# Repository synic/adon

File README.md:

adon
====

AVR Simon Clone

This is a simon clone written for AVR, specifically the ATTiny84a.  The schematic board in eagle/ has been designed to run off of 2 AA batteries, and the chip fuses in fuses.txt set the attiny84a to have a clock of 4mhz, and to have a brown out of 1.8 volts, meaning the batteries should last quite a while before they need to be replaced.

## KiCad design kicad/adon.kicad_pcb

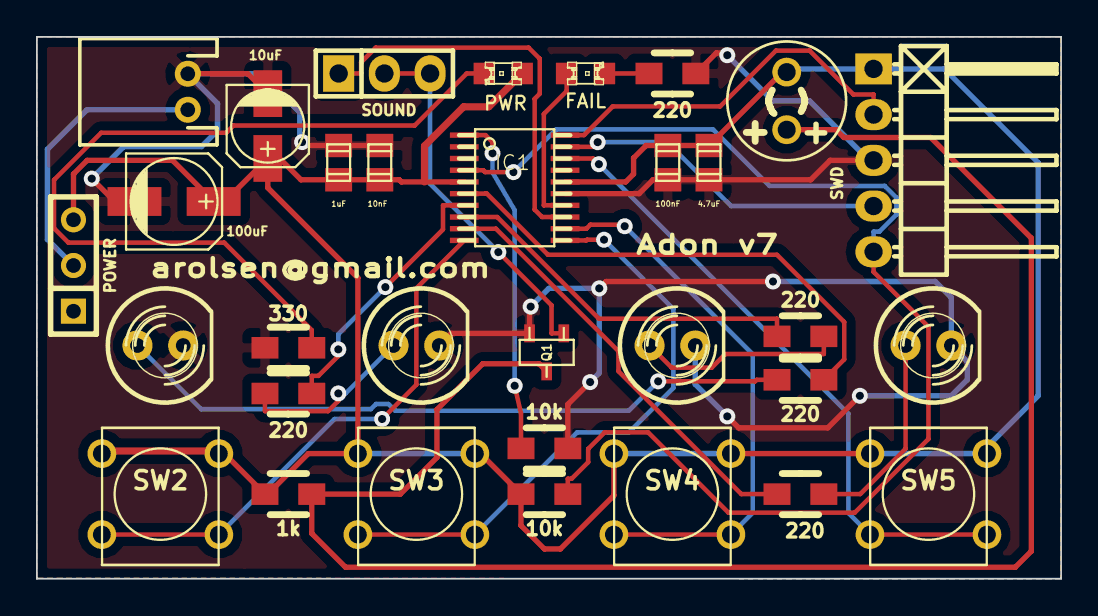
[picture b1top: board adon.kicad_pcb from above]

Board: 2 copper layers, 56.9 x 30.1 mm, 32 parts (0 on the bottom side), 25 nets.

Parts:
C1: 100uF; c_elec_5x5.3
C2: 1uF; c_0805
C3: 4.7uF; c_0805
C4: 10nF; c_0805
C5: 100nF; c_0805
C6: 10uF; c_elec_4x4.5
D1: PWR; LED-0805
D2: LED3; LED-5MM
D3: LED2; LED-5MM
D4: LED1; LED-5MM
D5: LED0; LED-5MM
D6: FAIL; LED-0805
IC1: STM32F030F4; AB2_TSSOP20
JP1: SOUND; Pin_Header_Straight_1x03
P1: BATTERY; jst-2-pth-ra
P3: SWD; Pin_Header_Angled_1x05
Q1: NPN2; sot23transistor
R1, R2: 10k; Resistor_SMD0805_HandSoldering
R3: 330; Resistor_SMD0805_HandSoldering
R4, R5, R6, R7, R9: 220; Resistor_SMD0805_HandSoldering
R8: 1k; Resistor_SMD0805_HandSoldering
SP1: SPEAKER; Buzzer_CUI_INC_CC-1601
SW1: POWER; MICROSWITCH_SPST
SW2: BUTTON0; SW_PUSH_SMALL
SW3: BUTTON1; SW_PUSH_SMALL
SW4: BUTTON2; SW_PUSH_SMALL
SW5: BUTTON3; SW_PUSH_SMALL

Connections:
GND: C1.2, C2.2, C3.1, C4.1, C5.1, C6.2, D2.2, D3.2, D4.2, D5.2, IC1.15, P1.2, P3.3, Q1.2, R1.2, R3.2, R9.2
NRST: IC1.4, P3.5, R2.1
unnamed: D1.2, R3.1
unnamed: D2.1, R4.2
unnamed: D3.1, R5.2
unnamed: D4.1, R6.2
unnamed: D5.1, R7.2
unnamed: D6.1, IC1.14
unnamed: D6.2, R9.1
unnamed: IC1.1, R1.1
unnamed: IC1.6, R7.1
unnamed: IC1.7, R6.1
unnamed: IC1.8, R5.1
unnamed: IC1.9, R4.1
unnamed: IC1.10, SW2.2
unnamed: IC1.11, SW3.2
unnamed: IC1.12, SW4.2
unnamed: IC1.13, JP1.1
unnamed: IC1.18, SW5.2
unnamed: JP1.2, JP1.3, Q1.1
unnamed: P1.1, SW1.2
unnamed: Q1.3, R8.2, SP1.2
SWCLK: IC1.20, P3.2
SWDIO: IC1.19, P3.4
VDD: C1.1, C2.1, C3.2, C4.2, C5.2, C6.1, D1.1, IC1.5, IC1.16, P3.1, R2.2, R8.1, SP1.1, SW1.3, SW2.1, SW3.1, SW4.1, SW5.1

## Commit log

2014-01-17 repo initial
2014-01-17 updated gitignore
2014-01-17 add eagle files
2014-01-17 comments
2014-01-19 woot
2014-01-20 add a 2 second delay after the game turns on to start playing
2014-01-20 add fuse support to Makefile
2014-01-23 done
2014-01-23 hopefully changes for 1mhz
2014-01-23 change bod to 2.7
2014-01-23 woot, got it down to 1mhz by setting prescaler to 64 instead of 1024
2014-01-23 these fuses are for attiny84a, not attiny84
2014-01-23 add the arduino version
2014-01-24 new board files
2014-01-24 add 3aa schematic and board
2014-01-26 board design is done
2014-01-27 add kicad files
2014-02-02 switch to avr dragon
2014-02-05 remove kicad stuff
2014-04-11 started on stm32 version
2014-04-11 stuff
2014-04-11 added old reference source
2014-04-11 delay function works now
2014-04-11 random number generator is working
2014-04-11 welp the simon part of it works!
2014-04-11 well hell, even the failed works
2014-04-11 even better
2014-04-12 it works. except for sound. boo.
2014-04-14 switch to timer 3
2014-04-26 better?
2014-04-26 sounds are done
2014-05-12 moved kicad dir to here
2014-05-12 modified gitignore
2014-05-18 change random rules
2014-05-18 fixed rand some more
2014-05-19 plz fix
2014-05-19 this seems to work even better for some reason:
